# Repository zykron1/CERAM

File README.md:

# CERAM
CERAM - Cost-Effective Rocket Aviation Module

## Why
Most rocket flight computers are made of SMD components and are designed to be made at scale by automated pick and place machines, but these methods are extremely expensive if you aren't manufacturing at scale.

## Schematic

## PCB

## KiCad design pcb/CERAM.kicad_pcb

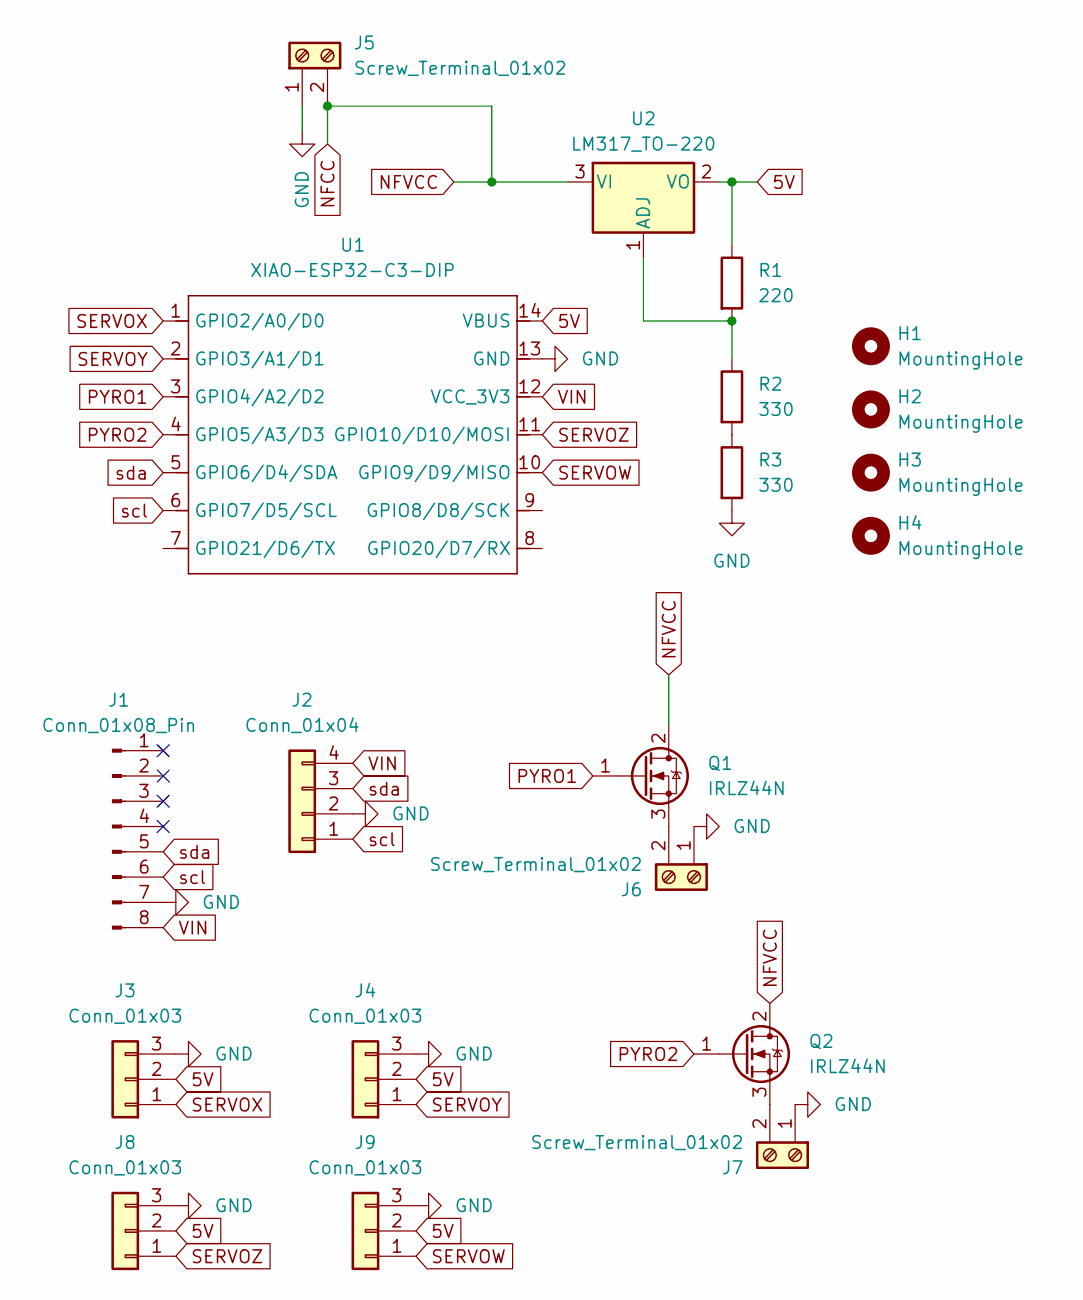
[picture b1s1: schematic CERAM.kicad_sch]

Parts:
H1, H2, H3, H4: MountingHole; MountingHole_3.2mm_M3
J1: Conn_01x08_Pin; PinHeader_1x08_P2.54mm_Vertical
J2: Conn_01x04; PinHeader_1x04_P2.54mm_Vertical
J3, J4, J8, J9: Conn_01x03; PinHeader_1x03_P2.54mm_Vertical
J5, J6, J7: Screw_Terminal_01x02; TerminalBlock_Xinya_XY308-2.54-2P_1x02_P2.54mm_Horizontal
Q1, Q2: IRLZ44N; TO-220-3_Vertical
R1: 220; R_Axial_DIN0207_L6.3mm_D2.5mm_P7.62mm_Horizontal
R2, R3: 330; R_Axial_DIN0207_L6.3mm_D2.5mm_P7.62mm_Horizontal
U1: XIAO-ESP32-C3-DIP; XIAO-ESP32C3-DIP
U2: LM317_TO-220; TO-220-3_Vertical

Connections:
5V: J3.2, J4.2, J8.2, J9.2, R1.1, U1.14 (VBUS), U2.2 (VO)
GND: J1.7, J2.2, J3.3, J4.3, J5.1, J6.1, J7.1, J8.3, J9.3, R3.2, U1.13 (GND)
NFCC: J5.2, Q1.2 (D), Q2.2 (D), U2.3 (VI)
unnamed: J6.2, Q1.3 (S)
unnamed: J7.2, Q2.3 (S)
unnamed: R2.2, R3.1
unnamed: R1.2, R2.1, U2.1 (ADJ)
PYRO1: Q1.1 (G), U1.3 (GPIO4/A2/D2)
PYRO2: Q2.1 (G), U1.4 (GPIO5/A3/D3)
SERVOW: J9.1, U1.10 (GPIO9/D9/MISO)
SERVOX: J3.1, U1.1 (GPIO2/A0/D0)
SERVOY: J4.1, U1.2 (GPIO3/A1/D1)
SERVOZ: J8.1, U1.11 (GPIO10/D10/MOSI)
VIN: J1.8, J2.4, U1.12 (VCC_3V3)
scl: J1.6, J2.1, U1.6 (GPIO7/D5/SCL)
sda: J1.5, J2.3, U1.5 (GPIO6/D4/SDA)

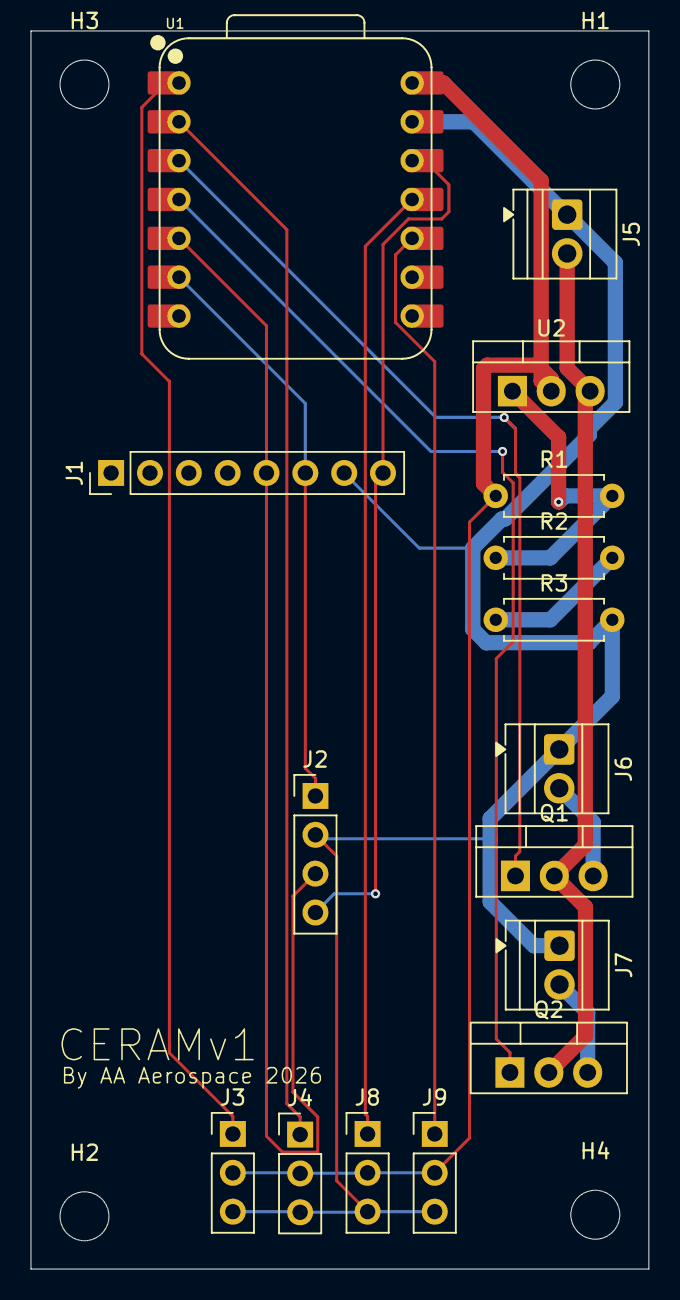
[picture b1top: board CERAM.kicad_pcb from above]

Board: 2 copper layers, 40.4 x 80.9 mm, 20 parts (0 on the bottom side), 16 nets.

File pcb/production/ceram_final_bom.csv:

Designator,Footprint,Quantity,Value,LCSC Part #
J1,PinHeader_1x08_P2.54mm_Vertical,1,Conn_01x08_Pin,
J2,PinHeader_1x04_P2.54mm_Vertical,1,Conn_01x04,
"J3, J4, J8, J9",PinHeader_1x03_P2.54mm_Vertical,4,Conn_01x03,
"J5, J6, J7",TerminalBlock_Xinya_XY308-2.54-2P_1x02_P2.54mm_Horizontal,3,Screw_Terminal_01x02,
"Q1, Q2",TO-220-3_Vertical,2,IRLZ44N,
R1,R_Axial_DIN0207_L6.3mm_D2.5mm_P7.62mm_Horizontal,1,220,
"R2, R3",R_Axial_DIN0207_L6.3mm_D2.5mm_P7.62mm_Horizontal,2,330,
U1,XIAO-ESP32C3-DIP,1,XIAO-ESP32-C3-DIP,
U2,TO-220-3_Vertical,1,LM317_TO-220,

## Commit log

2026-01-23 rough initial commit
2026-01-23 fixes
2026-01-23 images!
2026-01-23 typo fix
2026-01-23 firmware
2026-01-23 jlcpcb outputs
2026-01-23 updated bom with final totals
2026-06-22 cleanup
2026-06-22 accurate firmware
2026-06-22 forgot to remove build
